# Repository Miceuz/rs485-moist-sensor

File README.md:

# rs485 soil moisture sensor
Digital (RS485 - based) soil moisture and temperature sensor 

A version of [I2C soil moisture sensor](https://github.com/Miceuz/i2c-moisture-sensor) with several updates - antistatic protection, local voltage regulation and RS485 networking.

This is a contact-less capacitive soil moisture sensor, a continuation of my [I2C soil moisture sensor](https://github.com/Miceuz/i2c-moisture-sensor). This particular version of the sensor is suited for more professional installations where long cable runs is a requirement. It adds a local voltage regulator to mitigate the voltage drop and RS485 transceiver to accommodate long wires, also reverse polarity and an additional ESD protection level is added. 

This is the easiest and the most robust way to read soil moisture and temperature values into Raspberry Pi. I have written a [tutorial](https://github.com/Miceuz/rs485-moist-sensor/tree/master/tutorial) how to do it.

The main features:

 * Capacitive soil moisture sensing
 * Temperature sensing
 * Good stability with temperature
 * Good stability with power variation
 * Suitable for long cable runs
 * Uses industrial Modbus protocol

# Python library

A python library is available via pip. Type `pip install chirp_modbus` to install it. Check the [source code](https://github.com/Miceuz/rs485-moist-sensor/blob/master/utils/lib/chirp_modbus.py) for documentation. Usage example:
```python
from chirp_modbus import SoilMoistureSensor
s = SoilMoistureSensor(1, '/dev/ttyUSB5')
print(s.getTemperature())
print(s.getMoisture())
```

# Technical data

 * Supply voltage - 5V
 * Bus can be run on both 3V and 5V
 * Default serial settings: 19200, 8-bit frame, no parity, 2 stop bits
 * Default Modbus address: 1
 * Current consumption: Active: 9mA, Deep sleep: 11uA

## Principle of operation

Sensor makes periodic measurements (by default, once every 500ms), delays between measurements can be updated by writing to one of the Modbus registers. The results of the measurements are kept in specific Modbus registers and can be read by master any time unless the sensor is in deep sleep. 

Deep sleep is entered by writing a number of seconds to sleep into a special sleep register. The sensor will put the transceiver and all the periphery into the lowest possible power consumption mode and sleep for the specified amoutn of time. After the sleep the sensor will wake up, start taking measurements and be available on the bus till the next sleep command.

Serial communication parameters as baud rate, parity and address can be updated by writing to related registers. The sensor will reset and boot with the new parameters if any of those registers are written.

### Input (read only) registers

|Register number | Size (bytes) | Description |
|----------------|------------- |-------------|
|       0        |      2       | Soil moisture. Unsigned |
|       1        |      2       | Temperature. Signed. In tenths of degrees Celsius. I.e. 220 means 22.0C |

### Holding (read/write) registers

|Register number | Size (bytes) | Valid values | Default value | Description |
|----------------|--------------|------------- |---------------|-------------|
|        0       |       2      |  [1 - 247]   |      1        | Modbus address |
|        1       |       2      |  [0 - 7]     |      4        | Baud rate |
|        2       |       2      |  [0 - 2]     |      0        | Parity **Note: most cheap ebay USB to RS485 dongles don't support parity properly!** |
|        3       |       2      |  [1 - 65535] |     500       | Measurement interval in milliseconds |
|        4       |       2      |  [1 - 65535] |      0        | Time to sleep in seconds. Write to this register to put the sensor to sleep. |

#### Supported baudrates

 Number | Baudrate
--------|---------
   0    |  1200
   1    |  2400
   2    |  4800
   3    |  9600
   4    |  19200
   5    |  38400
   6    |  57600
   7    |  115200

#### Supported parity settings

 Number | Parity
--------|---------
   0    |  None
   1    |  Even
   2    |  Odd

**Note: most of the cheap ebay USB to RS485 dongles and/or their drivers do not support parity setting properly! You will have to use a proper parity supporting adapter to unbrick the sensor if you set this to something that your dongle does not support!** Luckily Adruino with ATmega 16u2 can be used as USB to Serial adapter to solve this.

## How to interpret the readings

Moisture values are relative. Meaning, more moisture will give you higher reading, less moisture - lower reading. It's up to you to calibrate it to amount of water in the soil as readings will be different for different types of soils. 

Moisture is somewhat linear. I test all sensors before shipping and they give about 292 in free air. 

Temperature is measured by the thermistor on the body of the sensor. Calculated absolute measurement accuracy is better than 2%. The returned value is in tenths of degrees Celsius. I.e. value 252 would mean 25.2°C.

## Controller support

The sensor will work fine with any controller supporting serial communication provided you have an RS485 transceiver. There are a lot of Modbus libraries readily available for a variety of micro-processor families. Thea easiest way to try the sensor is to use one of the abundant and cheap USB to RS485 dongles and connect it to a Raspberry pi or even directly to your computer. 

I have written some basic test code in python that is available on [github](https://github.com/Miceuz/i2c-moisture-sensor/blob/master/README.md) page. 

## Waterproofing

The sensor comes coated with PRF202 - a moisture resistant varnish for electronics. It's ok for play around in a flower pot but not enough for outdoor use. **You must add an additional protection to the whole sensor after soldering cable to it!** Some suggestions on making the sensor more robust after attaching the cable:

 * Polyester or epoxy resin - this method is the most bullet proof as the resin is totally resistant to the water. On the par side, note that sensitivity of the sensor will decrease depending on how thick the layer you are going to apply. Also applying the resin in uniform manner presents some challenge.
 * PlastiDip - some of my customers have tried this method - easy to apply by spraying and not a lot of loss of sensitivity.
 * Rubber balloon - yes, just roll a long balloon over the sensor :)  

Be sure to coat the whole thing - the sensor part, the electronics and the cable connection itself so no bare copper or solder is accessible to the water.

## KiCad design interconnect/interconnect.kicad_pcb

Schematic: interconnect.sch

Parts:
C1: C; C_0603_1608Metric_Pad1.05x0.95mm_HandSolder
J1, J2, J3: RJ45; RJ45_Amphenol_54602-x08_Horizontal

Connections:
GND: C1.2, J1.3, J1.5, J1.7, J2.3, J2.5, J3.3, J3.5, J3.7
unnamed: J1.1, J2.1
unnamed: J1.2, J2.2
unnamed: J2.7, J3.1
unnamed: J2.8, J3.2
VCC: C1.1, J1.4, J1.6, J1.8, J2.4, J2.6, J3.4, J3.6, J3.8

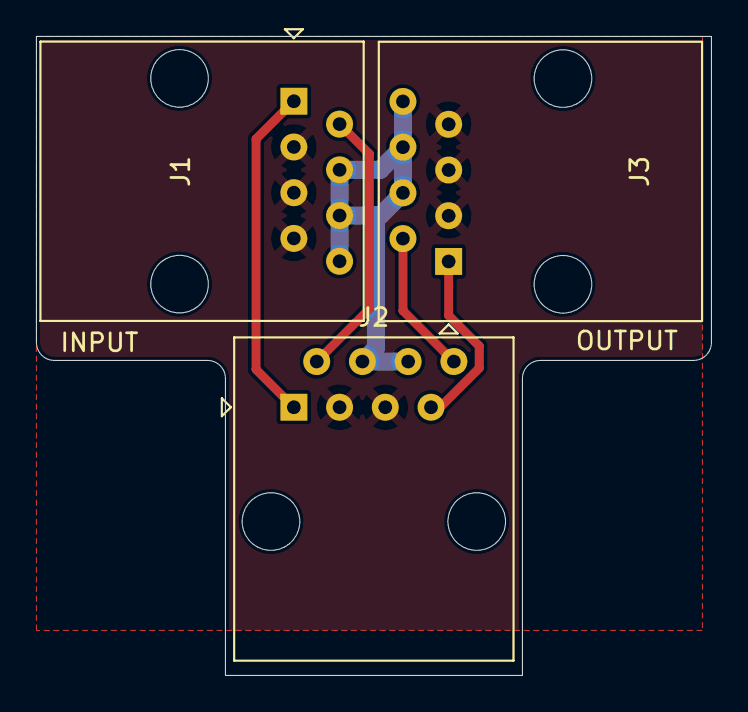
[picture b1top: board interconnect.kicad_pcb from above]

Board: 2 copper layers, 37.5 x 35.5 mm, 4 parts (1 on the bottom side), 6 nets.

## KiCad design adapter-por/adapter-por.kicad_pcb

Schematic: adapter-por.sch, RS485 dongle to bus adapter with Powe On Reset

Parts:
C1, C2, C3, C4, C5: C; C_0603_1608Metric
D1: LED; LED_0603_1608Metric
J1: Conn_01x04_Male; Pin_Header_Angled_1x04_Pitch2.54mm
J2: RJ45; RJ45_Amphenol_54602-x08_Horizontal
J3: Conn_01x02_Male; TerminalBlock_RND_205-00287_Pitch5.08mm
R1, R2, R3, R4, R5, R7: R; R_0603_1608Metric
R8: 120; R_0603_1608Metric
U1: MCP100; SOT-23
U2: MCP2505; SO-8_3.9x4.9mm_P1.27mm
U3, U4: SN74LVC1G3157; SOT-23-6

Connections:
/A: J1.2, U4.1 (B2)
/A_OUT: J2.1, R8.1, U4.4 (A)
/A_SW: C1.1, R1.1, U3.6 (S), U4.6 (S)
/B: J1.3, U3.1 (B2)
/B_OUT: J2.2, R8.2, U3.4 (A)
/VOUT: J2.4, J2.6, J2.8, U2.6 (OUT), U2.8 (OUT)
GND: C1.2, C2.2, C3.2, C4.2, C5.2, J1.4, J2.3, J2.5, J2.7, J3.1, R3.2, R4.2, R5.1, U1.3 (Vss), U2.3 (GND), U3.2 (GND), U4.2 (GND)
unnamed: C2.1, R2.2, R5.2, U2.1 (CTL)
unnamed: D1.1 (K), R7.2
unnamed: R1.2, R2.1, U1.1 (~RST)
unnamed: R3.1, U3.3 (B1)
unnamed: R4.1, U4.3 (B1)
unnamed: R7.1, U2.2 (FLG)
VCC: C3.1, D1.2 (A), J3.2, U1.2 (Vdd), U2.5 (IN), U2.7 (IN)
VDD: C4.1, C5.1, J1.1, U3.5 (Vcc), U4.5 (Vcc)

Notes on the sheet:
BRW

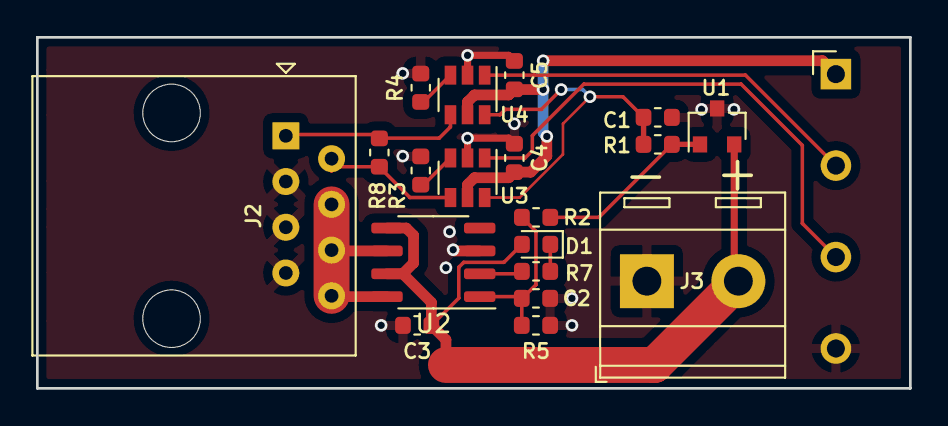
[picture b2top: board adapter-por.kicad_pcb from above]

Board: 2 copper layers, 48.5 x 19.5 mm, 20 parts (0 on the bottom side), 15 nets.

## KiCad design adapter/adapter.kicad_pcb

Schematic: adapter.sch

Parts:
J1: Conn_01x04_Male; Pin_Header_Angled_1x04_Pitch2.54mm
J2: RJ45; RJ45_Amphenol_54602-x08_Horizontal
J3: Conn_01x02_Male; TerminalBlock_RND_205-00287_Pitch5.08mm
JP1, JP2: Jumper_2_Open; SolderJumper-2_P1.3mm_Open_Pad1.0x1.5mm
JP3: Jumper_3_Bridged12; SolderJumper-3_P1.3mm_Bridged12_RoundedPad1.0x1.5mm_NumberL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

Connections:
/A: J1.2, J2.1
/A/GND: J2.7, JP2.1 (A)
/B: J1.3, J2.2
/B/VCC: J2.8, JP1.1 (A)
GND: J1.4, J2.3, J2.5, J3.2, JP2.2 (B)
unnamed: J1.1, JP3.1 (A)
unnamed: J3.1, JP3.3 (B)
VCC: J2.4, J2.6, JP1.2 (B), JP3.2 (C)

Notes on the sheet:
BRW

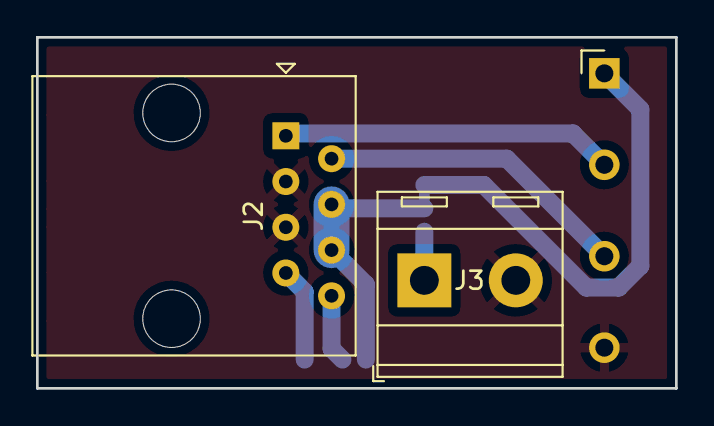
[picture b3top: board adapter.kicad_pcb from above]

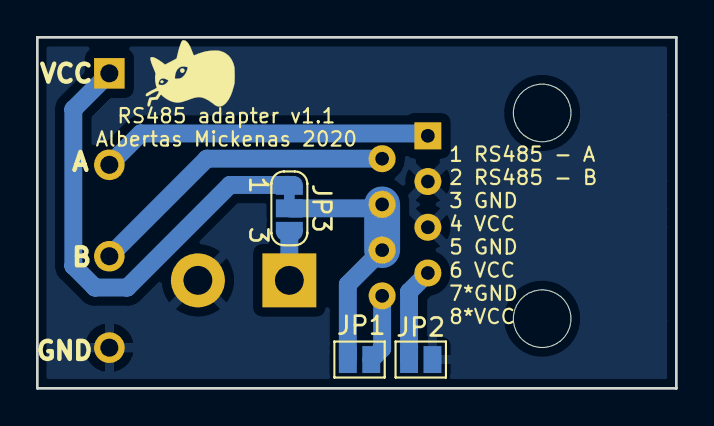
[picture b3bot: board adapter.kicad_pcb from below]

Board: 2 copper layers, 35.5 x 19.5 mm, 6 parts (3 on the bottom side), 8 nets.

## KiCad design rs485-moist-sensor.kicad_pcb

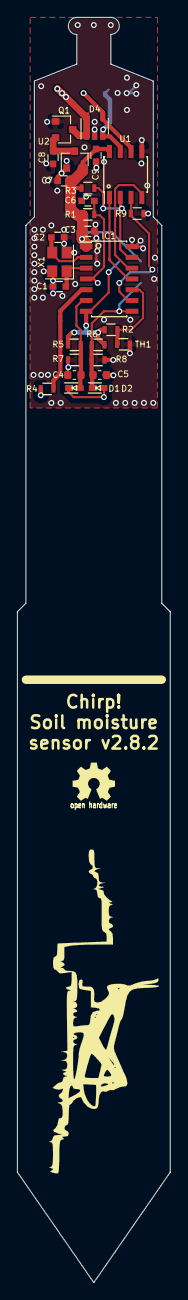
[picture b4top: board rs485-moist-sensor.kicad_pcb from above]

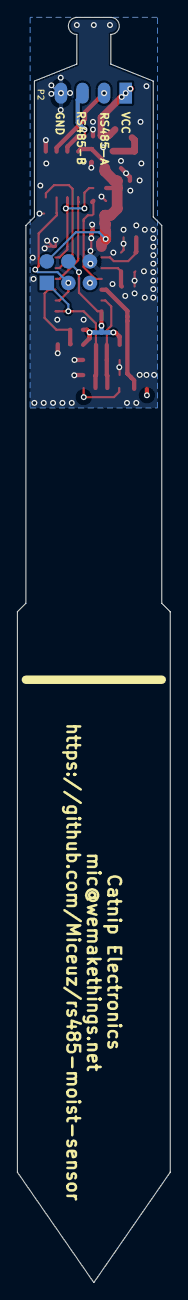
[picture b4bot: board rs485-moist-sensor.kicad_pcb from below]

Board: 4 copper layers, 18.0 x 149.0 mm, 29 parts (2 on the bottom side), 19 nets.

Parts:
C1, C2: 13p; C_0603
C3, C6, C7, C8, C9: 1u; C_0603
C4, C5: 1n; C_0603_1608Metric
D1, D2: RB751S40; SOD-523
D4: NUP4004M5T1G; SOT-23-5
IC1: ATTINY441-SSU; SOIC-14_3.9x8.7mm_Pitch1.27mm
P1: CONN_02X03; Pin_Header_Straight_2x03
P2: CONN_01X04; Pin_Header_Straight_1x04_Pitch2.54mm
Q1: Q_PMOS_GSD; SOT-23
R1, R3, R9: 10k; R_0603
R2: 10k 0.1%; R_0603
R4: 330; R_0603
R5, R6, R7, R8: 1M; R_0603
TH1: NCP18XH103F03RB; R_0603
U1: SN65HVD72; SOIC-8_3.9x4.9mm_Pitch1.27mm
U2: MCP1702; SOT-23
X1: 16MHz; Crystal_SMD_3225-4pin_3.2x2.5mm

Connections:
+3V3: C3.1, C7.1, C9.1, IC1.1, P1.2, R1.2, R3.1, U1.8, U2.2
/EXCITATION: IC1.5, R4.2
/MOSI: IC1.7, P1.4, R2.1, R5.2, R6.2
/RESET: C6.1, IC1.4, P1.5, R1.1
/RS485A: D4.4, P2.2, U1.6
/RS485B: D4.3, P2.3, U1.7
/RS485_READER_ENABLE: IC1.13, R3.2, U1.2
/RX: IC1.11, U1.1
/SCK: IC1.9, P1.3, R9.1, U1.3
/SENSE_HIGH/MISO: C5.1, D2.2, IC1.8, P1.1, R6.1, R8.2
/SENSE_LOW: C4.1, D1.1, IC1.6, R5.1, R7.2
/SENSOR_TRACK: D1.2, D2.1, R4.1
/THERMISTOR: IC1.10, R2.2, TH1.1
/TX: IC1.12, U1.4
GND: C1.2, C2.2, C3.2, C4.2, C5.2, C6.2, C7.2, C8.2, C9.2, D4.2, IC1.14, P1.6, P2.4, Q1.1, R7.1, R8.1, R9.2, TH1.2, U1.5, U2.1, X1.2, X1.4
unnamed: C1.1, IC1.3, X1.1
unnamed: C2.1, IC1.2, X1.3
unnamed: C8.1, Q1.2, U2.3
VCC: D4.1, D4.5, P2.1, Q1.3

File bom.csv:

Id,Designator,Package,Quantity,Designation,Supplier and ref,Available
1,P1,Pin_Header_Straight_2x03,1,CONN_02X03,,x
2,"D1,D2",SOD-523,2,BAT54,,x
3,IC1,QFN-20-1EP_4x4mm_Pitch0.5mm,1,ATTINY441-MU,,x
4,U1,SOIC-8_3.9x4.9mm_Pitch1.27mm,1,SP3481EN,,
5,X1,Crystal_HC49-SD_SMD,1,16MHz,,x
6,D3,LED-0603,1,LED,,x
7,P2,Pin_Header_Straight_1x04,1,CONN_01X04,,x
8,"C1,C2",C_0603,2,18p,,x
9,JP1,SMD-0603_r,1,JUMPER,,x
10,"C3,C6,C7",C_0603,3,1u,,x
11,"C4,C5",C_0603,2,1n,,x
12,R1,R_0603,1,10k,,x
13,R2,R_0603,1,10k 0.1%,,x
14,"R4,R9",R_0603,2,330,,x
15,"R5,R6,R7,R8",R_0603,4,1M,,x
16,R10,R_0603,1,120,,x
17,TH1,R_0603,1,THERMISTOR,,x
18,"REF**,REF**",MountingHole_3mm,2,MountingHole_3mm,,x

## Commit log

2015-02-16 Initial
2015-02-16 Add schematics PDF
2015-02-16 Add 3D render pic
2015-04-25 Move trace so that it does not touch a square MOSI pad
2015-04-25 Some most recent changes
2015-04-25 Add gerbers
2015-04-25 Add thermistor datasheet
2015-04-25 Some basic code - thermistor and capacitance readings work, rs485 works
2015-04-25 Remove some binary stuff
2015-04-26 Fiddle around with RS485 transceiver lib symbol -- pins were dangerously swapped!
2015-04-26 Move thermistor code to the separate module
2017-02-03 Specify thermistor
2017-02-03 Some minot firmware changes
2017-02-05 Add a local voltage regulator, add antistatic protection, specify transceiver, change attiny441 package to soic-14, route everything
2017-02-05 Remove outdated and generated stuff
2017-02-05 Ignore more
2017-02-05 Update pdf and png files
2017-02-05 fix linking, add pic in readme
2017-04-18 Added BOM from kicad generator
2017-04-18 Another board spin - add 3.3v regulator, other rs485 transceiver, esd protection
2017-04-18 Add part numbers and Farnell order numbers to the mail components
2017-04-24 Add a via so that programming header ground is connected
2017-04-24 There is no more led, pin assignments have changed
2017-04-25 Emable extended fuse programming in the Makefile, se BOD to enabled in active mode, to switched in power down mode
2017-04-25 Re-route TVS connection, hook up ground of the programming header
2017-04-25 Add a pulldown resistor to make transceiver more robust
2017-04-25 Remove generated file
2017-04-25 Pullup/pulldown resistors to put rs485 transceiver in off mode by default. Connect DE, ~RE lines to MCU separately. Provide power to resistive dividers from MCU, not from regulator to allow for lower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
2017-04-25 Add code after sleep modes investigation, supporting the latest changes in hardware
2017-04-25 Add manufacturing files
2017-04-25 Put values into place
2017-04-25 Add more manufacturing files: svg, closeup, part placement, readme
2017-04-26 Add code to stop excitation to the sleed function
2017-05-03 Fix the back silkscreen
2017-05-18 add modbus, add related fucntionality - measurements on intervals, deep sleep mode. Nothing is tested
2017-05-22 Change default baud rate, add bool as a type, shuffle stuff around. Should work but does not
2017-05-23 Smaller buffer! Some code reformatting. Some refactoring. A couple of new helper functions
2017-05-23 A bunch of changes comming with modbus integration: * RS485 direction control by using two separate receiver and transmitter control lines * Provide moisture in input register * Provide temperature i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
2017-05-23 Some python utilities for testing
2017-05-23 Extract measurement related stuff to a separate module
2017-05-23 Implement baud and parity setting, add stop bit handling as per Modbus specification
2017-05-23 Fix a buffer overflow
2017-05-24 Some refactoring to really understand what this modbus library is doing. It's crap, need to write one of my own after all
2017-05-25 addtempt to implement modbus on our own, something makes it work just once
2017-05-25 Clear timer otput capture flags as they are appearently set even without interrupts enabled
2017-05-25 Cleanup
2017-05-25 Loose the fight for parity - the most of cheap usb to serial dongles don't support even/odd parity properly, so drop the requirement to be even parity by default, and configure to use no parity by de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
2017-05-25 Use the new defaults in the test script: 19200/8-N-2
2017-06-19 Fix a missing ground connection. Make PCB updatable from schematics directly
2017-06-19 Add a step file of the sensor
2017-06-19 Add protective measures so that bogus data can not be loaded form eeprom even though it should never be able to get there. Make measurements after reset and after sleep to avoid potential long wait f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
2017-06-20 Move python utils to a separate folder
2017-06-20 Readme for utils
2017-06-20 fix heading
2017-06-20 Update README.md
    fix link
2017-06-26 Be more robust, wait until something is on the bus
2017-06-28 Initialize the settings to defaults more vigoriously, including measurement interval. Enable reader, not driver
2017-06-28 Longer startup time to accomodate crystals from supplier
2017-06-28 Sleep a bit more in the test script
2017-08-30 Start writing a tutorial
2017-09-12 Fix a shameful error of not have being tested full functionality after the huge refactoring
2017-10-12 add utility for address setting
2017-10-12 Add utility for address change functionality testing
2017-10-12 Add utility for baut setting
2017-10-12 Cleanup test scirpt
2017-10-12 A STEP file
2017-10-13 Enable the watchdog in fuses, set it up to 2s timeout. Just for testing now
2017-10-13 Disable WDT in fuses as this does not allow us to use WDT interrupt. Add a method to check if all the communicaiton is done before going to sleep. Fix sleep functionality so that the sensor sleeps ex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
2017-10-13 Add sleep functionality testing code
2017-10-13 Add FW version input register
2017-10-13 Add a Python library wrapping all the communication details
2017-10-13 Update documentation to reflect the newly available Python library
2017-10-21 Fix tables in README.md
2018-09-03 Changed crystal to SMD 3225
2018-09-04 added 3d model for crystal SMD 3225
2018-09-04 4 layer configuration
2018-09-05 GND into inner layers
2018-09-05 gerbers and drill files
2018-09-11 New kicad library order
2018-09-11 Small changes to util scripts making them a bit more friendly for debug purposes
2018-09-11 Lost commit - symbol lib table
2018-09-11 Add measurement data
2018-09-11 Fill zones
2019-02-04 removed .vscode
2019-02-12 Added documentation for input registers
    Added documentation for input registers
2019-02-12 Revert "Update main.c"
    This reverts commit b15309eba4051b767dadc95ee9e7d43acde72982.
2019-02-12 Revert "Revert "Update main.c""
    This reverts commit d38ea03a0ac59e6fba940e009b52698acc5a1b75.
2019-02-13 Final commit for the night
    After further research it looks likes the interrupt bits need to be cleared and reset when eeprom is written to to prevent memory corruption in case an interrupt fires during a write operation. Also 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
2019-02-14 Changes for write protected (WDE) registers
    Changes for write protected (WDE) registers.
2019-02-18 corrected boolean function primative mismatch for u16.
    Corrected boolean function primative mismatch for u16.
    CCP signature ignores interrupt flags by default so removed the SREG CLI, SEI function calls.
    Added unhandled exception to modbusGet().
2019-02-19 update gitignore for atsln and cproj
    update gitignore for atsln and cproj
2019-03-01 storage optimization
    Added compare values to saveConfig() to check if the value needed to be updated before an attempted write.
2019-03-01 More compact, efficent solution to storage using update instead of force write.
    According to the library's documentation:
    "In addition to the write functions there is a set of update ones. This functions read each byte first and skip the burning if the old value is the same with new. The scaning direction is from high a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
2019-03-03 Update chirp_modbus.py
    Fix resigter numbers in the python library. Close #2
2019-03-05 Clarified astruct sleepTimeSec vs variable sleeptimes
    Clarified astruct sleepTimeSec vs variable sleeptimes
2019-03-05 removed exception code
    removed exception code
2019-08-27 Fix tutorial by adding argument labels to constructor call
2019-08-27 Attempt to un-suckify the scanBus method by not hardcoding serial port and allowing to specify some of the serial port parameters.
2019-08-27 Fix busScan documentation in tutorial, add another example of sensor data being pushed to InfluxDB
2019-08-29 Python library - move to minimalmodbus 1.0.2 as it was breaking the previous version, bump version to 1.0.1
2019-10-08 Sleep less
2019-10-08 Add crystal model
2019-10-22 Update the sensor outline to accomodate narrower heatshrink. Also change ziptie application feature
2019-10-22 Ignore schematics backups
2019-10-22 Update capacitance to accomodate crystal change. Tidyup fabrication layers
2020-01-24 Add sensor RJ45 interconnect board
2020-01-24 Remove gerbers as they are generated
2020-01-28 Add RJ45 adapter board to RS485 dongle
2020-01-28 Export schematics PDF that looks a bit better
2020-02-10 Update README.md
    Fix a typo
2020-02-10 Relabel nets
2020-03-12 Add some adapter and interconnect pics
2020-03-12 Kicad version shifting junk
2020-03-12 Add more python utils
2020-03-12 Fix up the test utility
2020-03-17 Play around in python scripts a bit
2020-03-18 Release a new library version to properly use the current version of minimalmodbus
2020-03-18 Update python tools to use the new library, add more arguments, less hardcoded stuff
2020-03-22 Just one fix
2020-03-22 Chase KiCad file updates
2020-04-03 Add cable marker link
2020-04-03 Add adapter with Power On Reset circuit to maybe mitigate eeprom corruption problem in current FW batch
2020-04-09 Sleep less in test utility
2020-04-26 Use generic gcc with no hardcoded version
2020-04-26 POR adapter fixups
2020-04-26 Fix a variable with no type
2020-10-20 Add step models for rj45 connectors
2020-12-22 Make python3 compatible
2021-03-11 Add Arduino example that communicated to the sensor
2023-10-16 Change defaut port number, update to python 3 prints
2023-12-04 Add cable pinout to sensor schematics
